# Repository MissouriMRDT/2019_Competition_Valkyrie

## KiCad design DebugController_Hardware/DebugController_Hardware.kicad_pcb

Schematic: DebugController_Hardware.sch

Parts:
C1, C2: 10uf; C_0603_1608Metric_Pad1.05x0.95mm_HandSolder
Conn1: AndersonPP; Anderson_2_Horisontal_Side_by_Side
D1, D2, D3, D4, D5, D6, D7, D8, D9, D10, D11, D12, D13, D14, D15, D16, D17, D18, D19, D20, D21, D22, D23, D24, D25, D26, D27, D28, D30: LED; LED_0603_1608Metric_Pad1.05x0.95mm_HandSolder
R1, R2, R3, R4, R5, R6, R7, R8, R9, R10, R11, R12, R13, R14, R15, R16, R17, R18, R19, R20, R21, R22, R23, R24, R25, R26, R27, R28, R29: 500; R_0603_1608Metric_Pad1.05x0.95mm_HandSolder
RV1: R_POT; Potentiometer_Bourns_PTV09A-1_Single_Vertical
SW1, SW2, SW3, SW4, SW5, SW6, SW7, SW8, SW9, SW10, SW11, SW12, SW13, SW14, SW15, SW16, SW17, SW18, SW19, SW20, SW21, SW22, SW23: SW_Push; SW_SPST_PTS645
U1: TM4C129E_Launchpad; TM4C129E_Launchpad_FULL_Bottom_SMD
U2: OKI; OKI_Horizontal

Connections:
+3V3: C2.1, R5.1, RV1.1, SW1.1, SW2.1, SW3.1, SW4.1, SW5.1, SW6.1, SW7.1, SW8.1, SW9.1, SW10.1, SW11.1, SW12.1, SW13.1, SW14.1, SW15.1, SW16.1, SW17.1, SW18.1, SW19.1, SW20.1, SW21.1, SW22.1, SW23.1, U1.+3V3, U2.3 (Vo)
Arm_1: R12.1, SW7.2, U1.PE0
Arm_2: R13.1, SW8.2, U1.PE1
Arm_3: R14.1, SW9.2, U1.PE2
Arm_4: R15.1, SW10.2, U1.PE3
Arm_5: R17.1, SW11.2, U1.PD7
Arm_6: R18.1, SW12.2, U1.PA6
Arm_7: R19.1, SW13.2, U1.PM4
Arm_8: R20.1, SW14.2, U1.PM5
Arm_Ind: R10.1, U1.PB5
Drive_1: R1.1, SW1.2, U1.PE4
Drive_2: R3.1, SW2.2, U1.PC4
Drive_3: R4.1, SW3.2, U1.PC5
Drive_4: R7.1, SW4.2, U1.PC6
Drive_5: R8.1, SW5.2, U1.PE5
Drive_6: R9.1, SW6.2, U1.PD3
Drive_Ind: R6.1, U1.PB4
unnamed: C1.1, U2.1 (Vi)
unnamed: D1.2 (A), R2.2
unnamed: D2.2 (A), R1.2
unnamed: D3.2 (A), R3.2
unnamed: D4.2 (A), R4.2
unnamed: D5.2 (A), R5.2
unnamed: D6.2 (A), R6.2
unnamed: D7.2 (A), R7.2
unnamed: D8.2 (A), R8.2
unnamed: D9.2 (A), R9.2
unnamed: D10.2 (A), R10.2
unnamed: D11.2 (A), R11.2
unnamed: D12.2 (A), R12.2
unnamed: D13.2 (A), R13.2
unnamed: D14.2 (A), R14.2
unnamed: D15.2 (A), R15.2
unnamed: D16.2 (A), R16.2
unnamed: D17.2 (A), R17.2
unnamed: D18.2 (A), R18.2
unnamed: D19.2 (A), R19.2
unnamed: D20.2 (A), R20.2
unnamed: D21.2 (A), R21.2
unnamed: D22.2 (A), R22.2
unnamed: D23.2 (A), R23.2
unnamed: D24.2 (A), R24.2
unnamed: D25.2 (A), R25.2
unnamed: D26.2 (A), R26.2
unnamed: D27.2 (A), R27.2
unnamed: D28.2 (A), R28.2
unnamed: D30.2 (A), R29.2
Other_1: R25.1, SW19.2, U1.PD1
Other_2: R26.1, SW20.2, U1.PD0
Other_3: R27.1, SW21.2, U1.PN2
Other_4: R28.1, SW22.2, U1.PN3
Other_Ind: R16.1, U1.PK1
Pot_Ind: R2.1, U1.PA5
Pot_Out: RV1.2, U1.PD5
SRA_1: R21.1, SW15.2, U1.PF1
SRA_2: R22.1, SW16.2, U1.PF2
SRA_3: R23.1, SW17.2, U1.PF3
SRA_4: R24.1, SW18.2, U1.PG0
SRA_Ind: R11.1, U1.PK0
Stop: R29.1, SW23.2

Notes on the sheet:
Yellow
Drive System
Arm System
Buttons
SRA System
Other Systems
TIVAs
Stop
Potentiometer
3.3V
Power Conversion
Green
Power
Pot_Ind
LEDs
Blue
Drive
Arm
SRA
Other

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
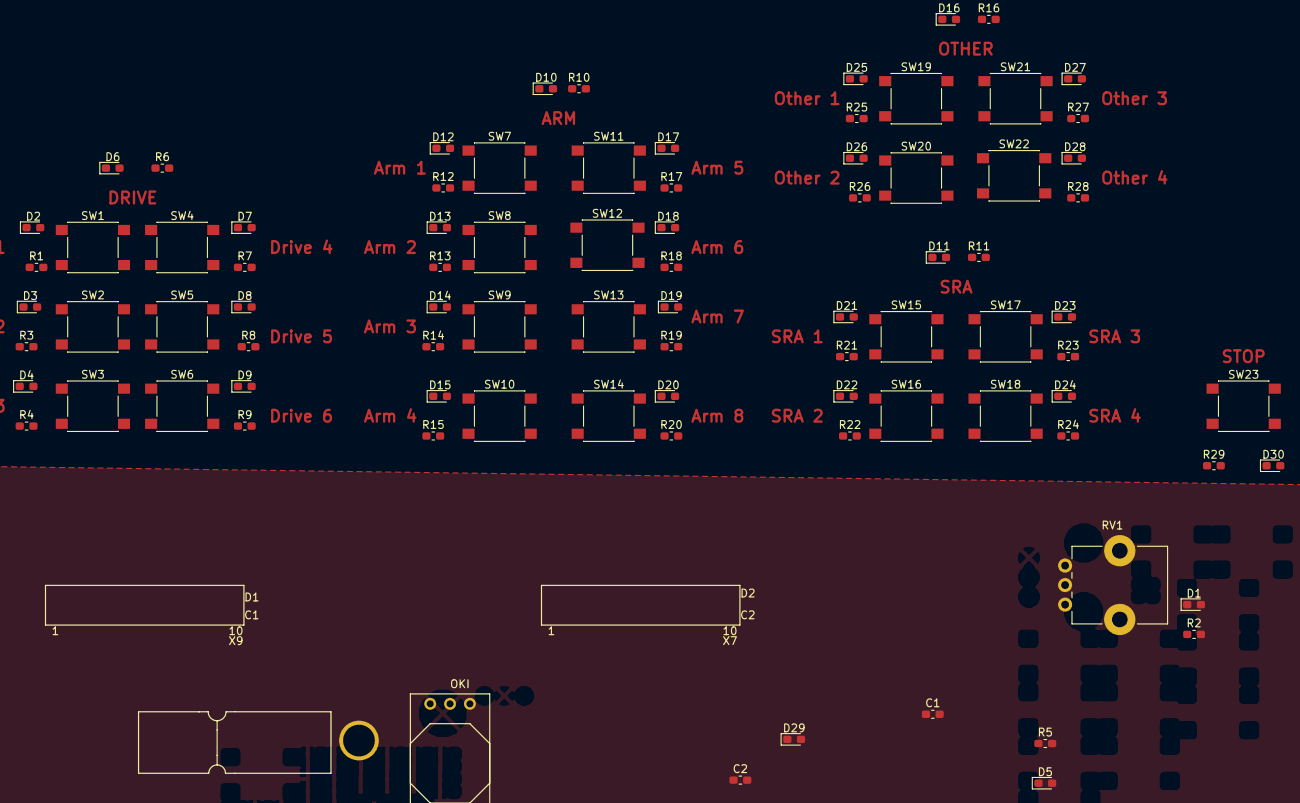
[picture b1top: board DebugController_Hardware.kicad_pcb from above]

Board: 2 copper layers, 88 parts (0 on the bottom side), 61 nets, no tracks yet.

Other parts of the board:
D29: LED; LED_0603_1608Metric_Pad1.05x0.95mm_HandSolder

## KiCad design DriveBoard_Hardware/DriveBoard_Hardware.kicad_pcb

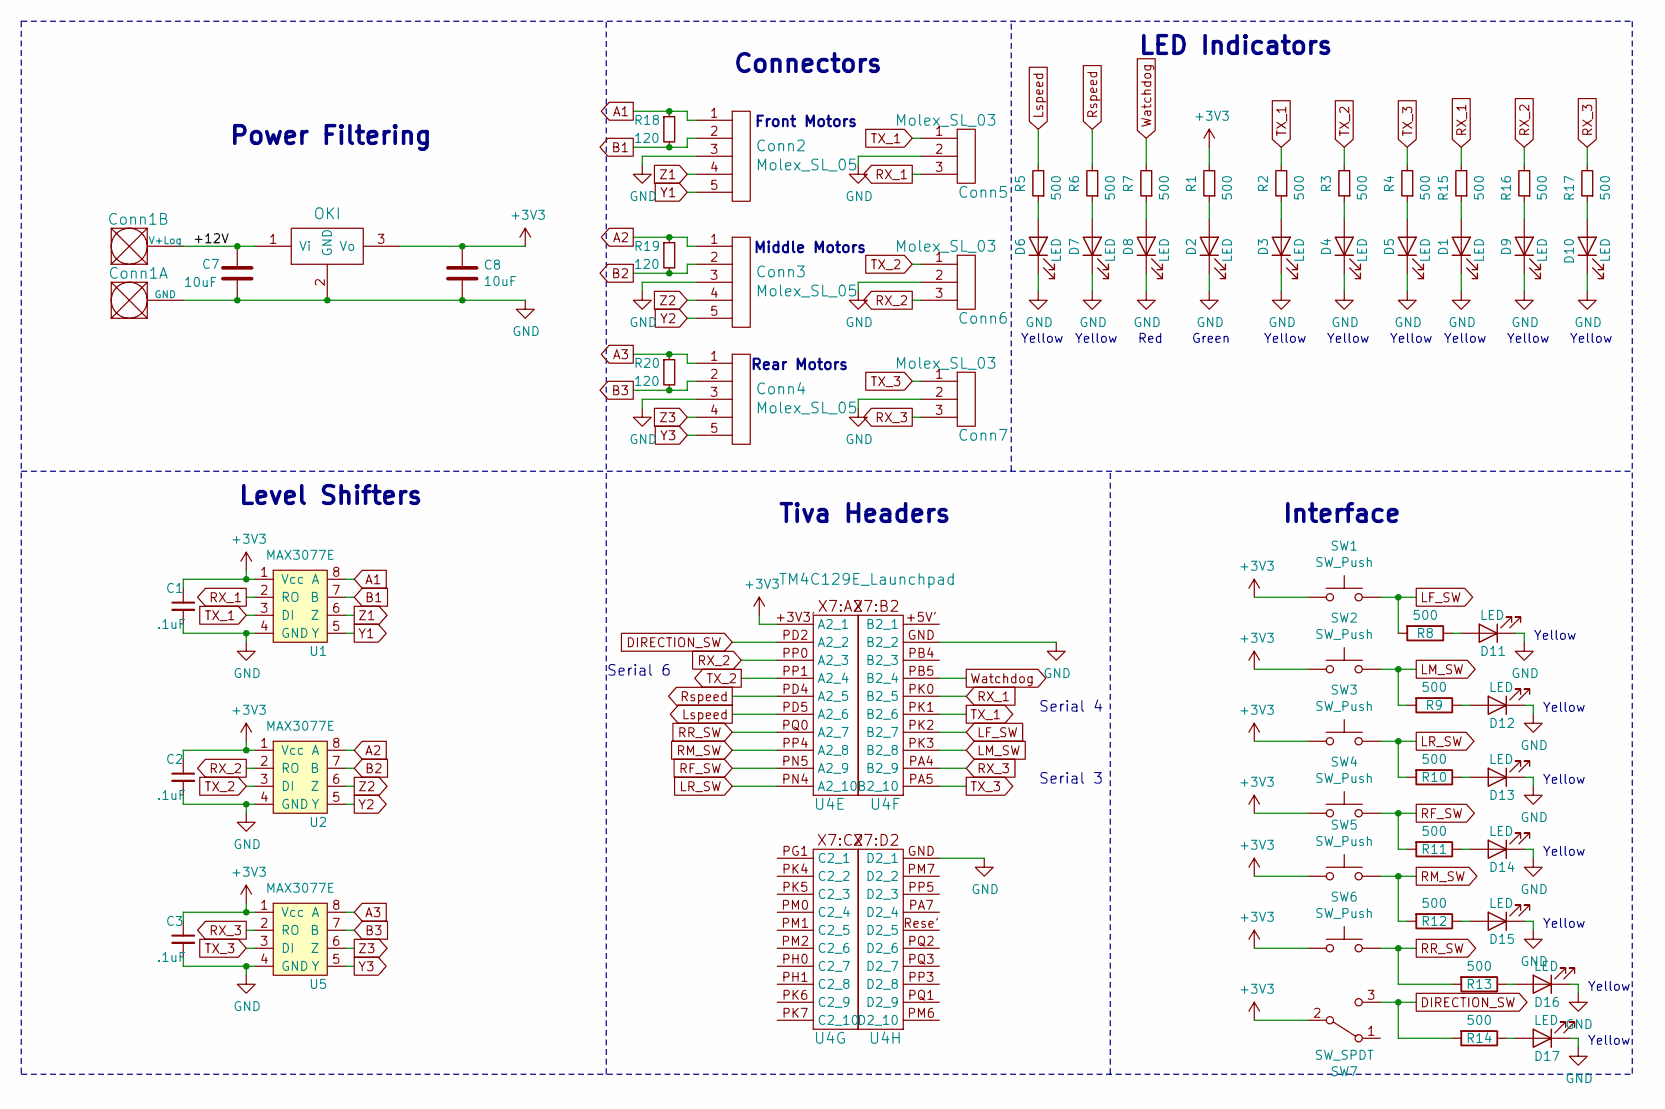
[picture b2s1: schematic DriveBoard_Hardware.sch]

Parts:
C1, C2, C3: .1uF; C_0603_1608Metric_Pad1.05x0.95mm_HandSolder
C7, C8: 10uF; C_0603_1608Metric_Pad1.05x0.95mm_HandSolder
Conn1: AndersonPP; Anderson_2_Horizontal_Side_by_Side
Conn2, Conn3, Conn4: Molex_SL_05; MOLEX_SL_05_Horizontal
Conn5, Conn6, Conn7: Molex_SL_03; MOLEX_SL_03_Horizontal
D1, D2, D3, D4, D5, D6, D7, D8, D9, D10, D11, D12, D13, D14, D15, D16, D17: LED; LED_0603_1608Metric_Pad1.05x0.95mm_HandSolder
R1, R2, R3, R4, R5, R6, R7, R15, R16, R17: 500; LED_0603_1608Metric_Pad1.05x0.95mm_HandSolder
R8, R9, R10, R11, R12, R13, R14: 500; R_0603_1608Metric_Pad1.05x0.95mm_HandSolder
R18, R19, R20: 120; R_0603_1608Metric_Pad1.05x0.95mm_HandSolder
SW1, SW2, SW3, SW4, SW5, SW6: SW_Push; SW_SPST_TL3305A
SW7: SW_SPDT; SW_CuK_OS102011MA1QN1_SPDT_Angled
U1, U2, U5: MAX3077E; SOIC-8_3.9x4.9mm_P1.27mm
U3: OKI; OKI_Horizontal
U4: TM4C129E_Launchpad; TM4C129E_Launchpad_X7_SMD_BOTTOM

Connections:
+3V3: C1.1, C2.1, C3.1, C8.1, R1.2, SW1.1, SW2.1, SW3.1, SW4.1, SW5.1, SW6.1, SW7.2 (B), U1.1 (Vcc), U2.1 (Vcc), U3.3 (Vo), U4.+3V3' (A2_1), U5.1 (Vcc)
/+12V: C7.1, Conn1.2 (V+Log), U3.1 (Vi)
A1: Conn2.1, R18.1, U1.8 (A)
A2: Conn3.1, R19.1, U2.8 (A)
A3: Conn4.1, R20.1, U5.8 (A)
B1: Conn2.2, R18.2, U1.7 (B)
B2: Conn3.2, R19.2, U2.7 (B)
B3: Conn4.2, R20.2, U5.7 (B)
DIRECTION_SW: R14.2, SW7.3 (C), U4.PD2 (A2_2)
GND: C1.2, C2.2, C3.2, C7.2, C8.2, Conn1.1 (GND), Conn2.3, Conn3.3, Conn4.3, Conn5.2, Conn6.2, Conn7.2, D1.1 (K), D2.1 (K), D3.1 (K), D4.1 (K), D5.1 (K), D6.1 (K), D7.1 (K), D8.1 (K), D9.1 (K), D10.1 (K), D11.1 (K), D12.1 (K), D13.1 (K), D14.1 (K), D15.1 (K), D16.1 (K), D17.1 (K), U1.4 (GND), U2.4 (GND), U3.2 (GND), U4.GND (B1_2), U5.4 (GND)
LF_SW: R8.2, SW1.2, U4.PK2 (B2_7)
LM_SW: R9.2, SW2.2, U4.PK3 (B2_8)
LR_SW: R10.2, SW3.2, U4.PN4 (A2_10)
Lspeed: R5.2, U4.PD5 (A2_6)
unnamed: D1.2 (A), R15.1
unnamed: D2.2 (A), R1.1
unnamed: D3.2 (A), R2.1
unnamed: D4.2 (A), R3.1
unnamed: D5.2 (A), R4.1
unnamed: D6.2 (A), R5.1
unnamed: D7.2 (A), R6.1
unnamed: D8.2 (A), R7.1
unnamed: D9.2 (A), R16.1
unnamed: D10.2 (A), R17.1
unnamed: D11.2 (A), R8.1
unnamed: D12.2 (A), R9.1
unnamed: D13.2 (A), R10.1
unnamed: D14.2 (A), R11.1
unnamed: D15.2 (A), R12.1
unnamed: D16.2 (A), R13.1
unnamed: D17.2 (A), R14.1
RF_SW: R11.2, SW4.2, U4.PN5 (A2_9)
RM_SW: R12.2, SW5.2, U4.PP4 (A2_8)
RR_SW: R13.2, SW6.2, U4.PQ0 (A2_7)
RX_1: Conn5.3, R15.2, U1.2 (RO), U4.PK0 (B2_5)
RX_2: Conn6.3, R16.2, U2.2 (RO), U4.PP0 (A2_3)
RX_3: Conn7.3, R17.2, U4.PA4 (B2_9), U5.2 (RO)
Rspeed: R6.2, U4.PD4 (A2_5)
TX_1: Conn5.1, R2.2, U1.3 (DI), U4.PK1 (B2_6)
TX_2: Conn6.1, R3.2, U2.3 (DI), U4.PP1 (A2_4)
TX_3: Conn7.1, R4.2, U4.PA5 (B2_10), U5.3 (DI)
Watchdog: R7.2, U4.PB5 (B2_4)
Y1: Conn2.5, U1.5 (Y)
Y2: Conn3.5, U2.5 (Y)
Y3: Conn4.5, U5.5 (Y)
Z1: Conn2.4, U1.6 (Z)
Z2: Conn3.4, U2.6 (Z)
Z3: Conn4.4, U5.6 (Z)

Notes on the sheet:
Connectors
Tiva Headers
Power Filtering
Level Shifters
Front Motors
Middle Motors
Rear Motors
Serial 4
Serial 3
Serial 6
LED Indicators
Interface
Yellow
Green
Red

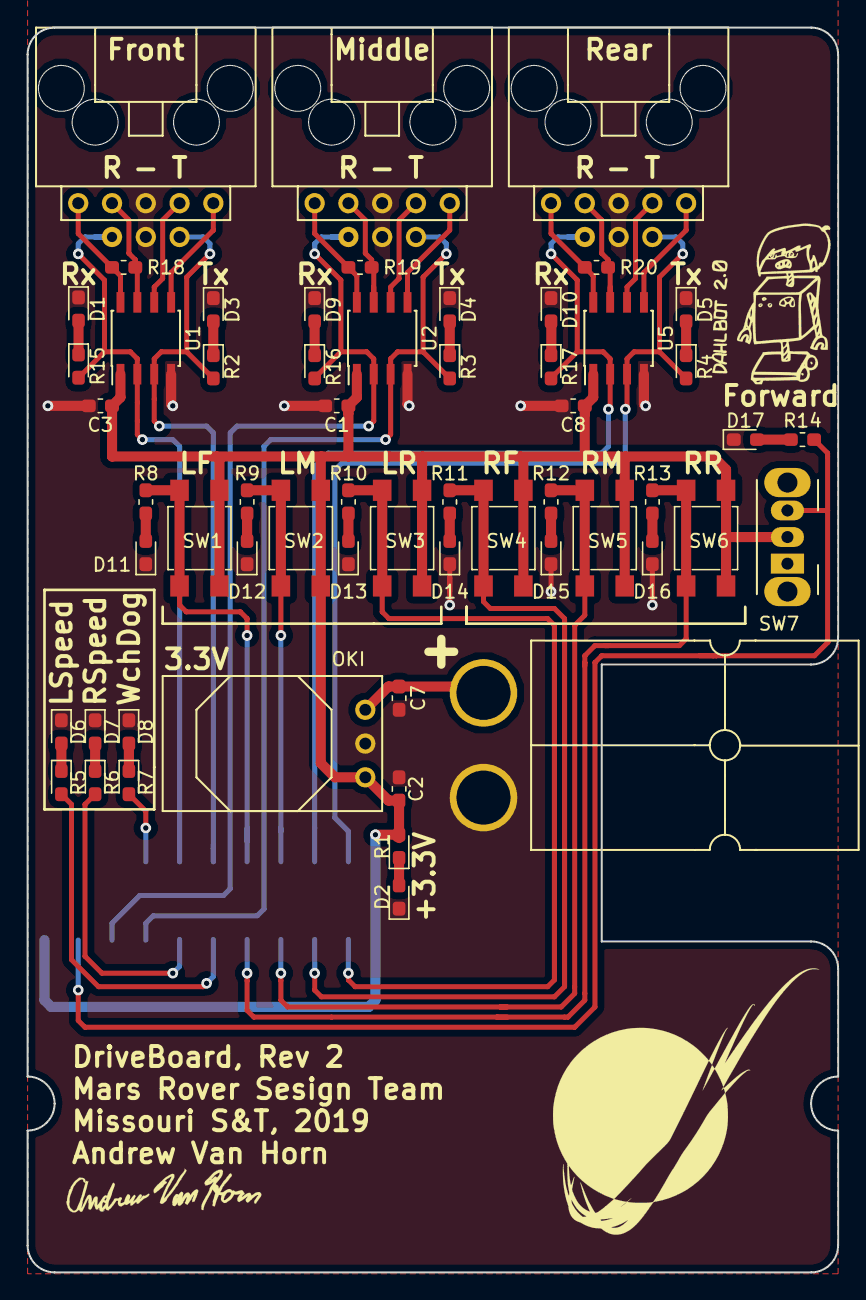
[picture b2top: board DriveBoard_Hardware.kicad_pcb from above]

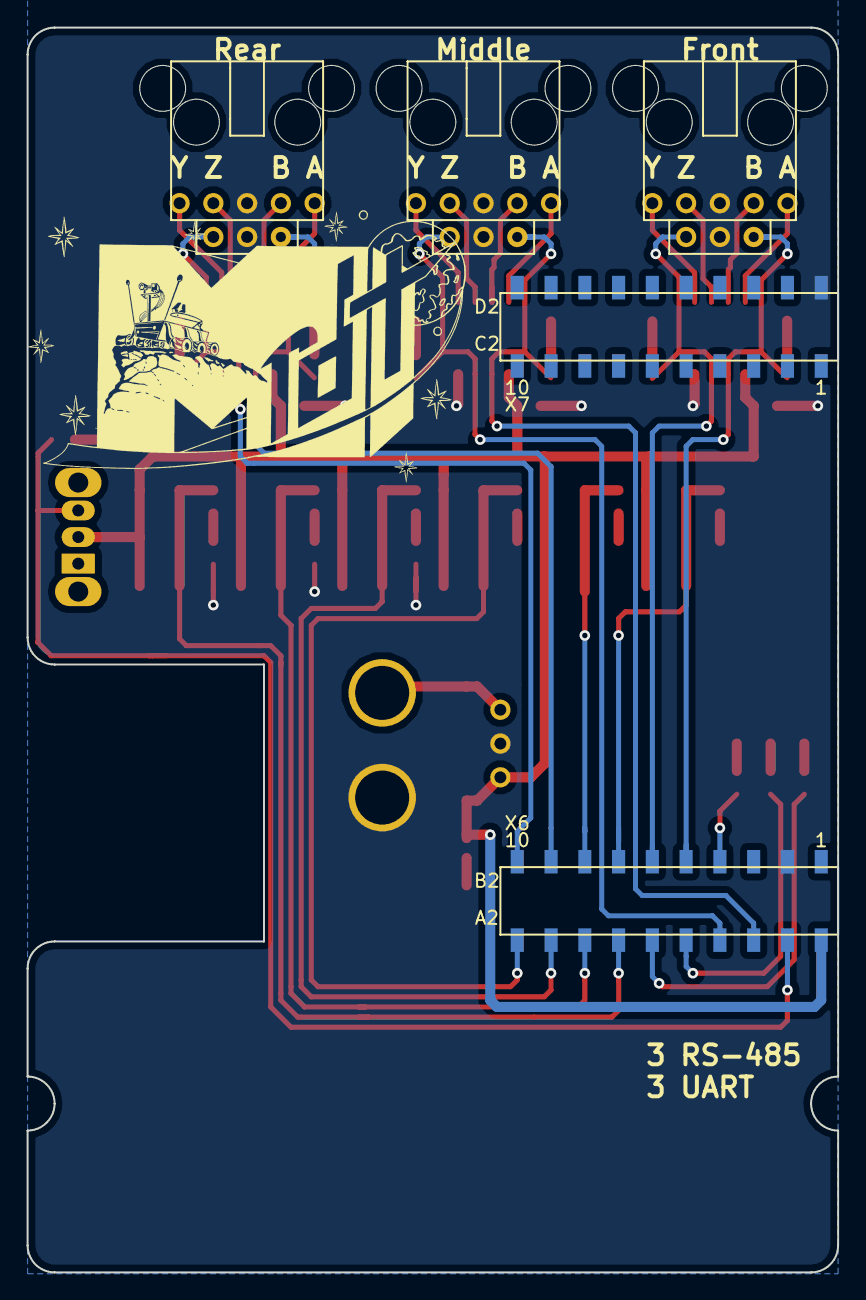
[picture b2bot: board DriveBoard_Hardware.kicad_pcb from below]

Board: 2 copper layers, 61.0 x 93.6 mm, 61 parts (3 on the bottom side), 48 nets.

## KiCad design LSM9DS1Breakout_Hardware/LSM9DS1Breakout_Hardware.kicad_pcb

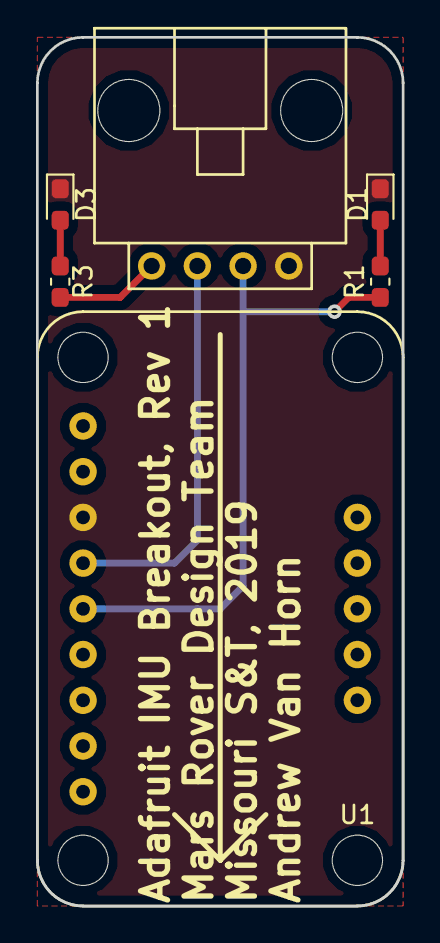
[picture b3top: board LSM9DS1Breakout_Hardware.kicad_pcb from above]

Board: 2 copper layers, 20.3 x 48.3 mm, 6 parts (0 on the bottom side), 6 nets.

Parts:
Conn1: Molex_SL_04; MOLEX_SL_04_Horizontal
D1, D3: LED; LED_0603_1608Metric_Pad1.05x0.95mm_HandSolder
R1, R3: 500; R_0603_1608Metric_Pad1.05x0.95mm_HandSolder
U1: Adafruit_LSM9DS1

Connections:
+5V: Conn1.1, R3.1, U1.1
GND: Conn1.4, D1.1, D3.1, U1.3
unnamed: D1.2, R1.2
unnamed: D3.2, R3.2
SCL: Conn1.2, U1.4
SDA: Conn1.3, R1.1, U1.5

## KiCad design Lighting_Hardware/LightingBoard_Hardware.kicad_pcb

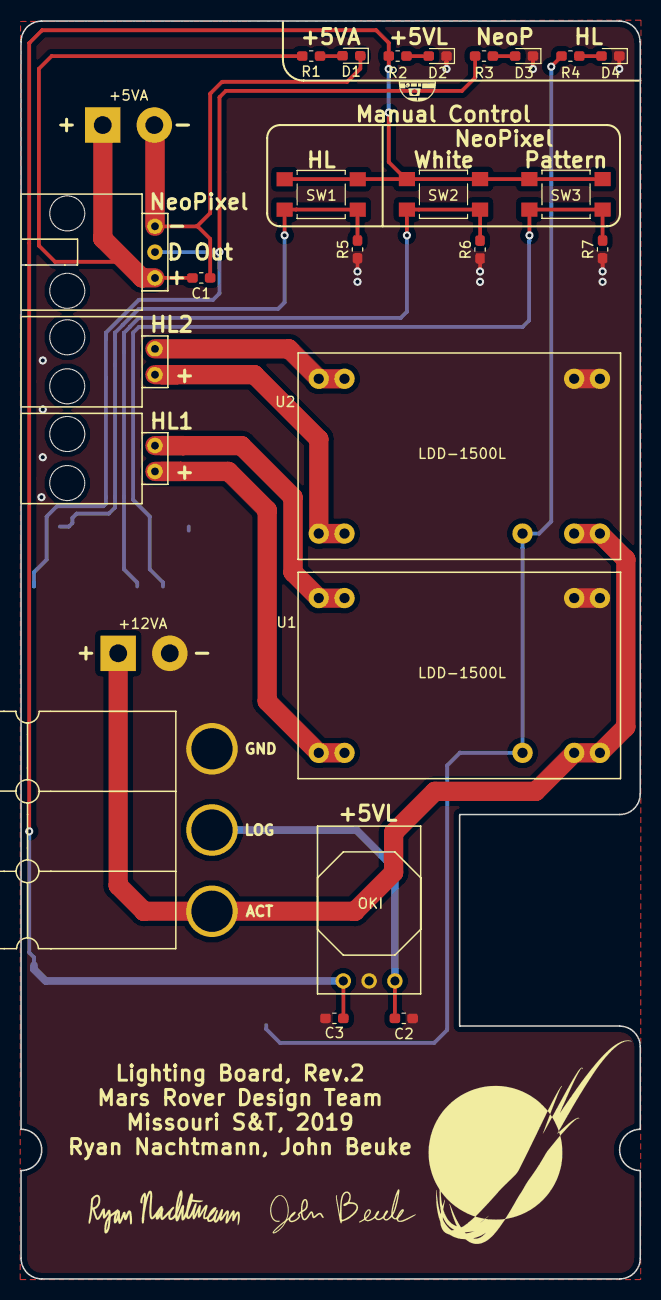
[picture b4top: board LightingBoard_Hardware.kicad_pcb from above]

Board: 2 copper layers, 61.0 x 123.8 mm, 27 parts (0 on the bottom side), 19 nets.

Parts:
+5VA, +12VA: SolderWirePad_1x02_P5.08mm_Drill1.5mm
C1, C2, C3: 10uF; C_0603_1608Metric_Pad1.05x0.95mm_HandSolder
Conn1: AndersonPP; Anderson_3_Horisontal_Side_by_Side
Conn2, Conn3: Molex_SL_02; MOLEX_SL_02_Horizontal
Conn4: Molex_SL_03; MOLEX_SL_03_Horizontal
D1, D2: G_LED; LED_0603_1608Metric_Pad1.05x0.95mm_HandSolder
D3, D4: Org_LED; LED_0603_1608Metric_Pad1.05x0.95mm_HandSolder
R1, R2, R3, R4: 500; R_0603_1608Metric_Pad1.05x0.95mm_HandSolder
R5, R6, R7: 10K; R_0603_1608Metric_Pad1.05x0.95mm_HandSolder
SW1, SW2, SW3: SW_Push; SW_SPST_TL3305A
U1, U2: LDD-1500L; LDD-1500L_LED_DRIVER
U3: TM4C129E_Launchpad; TM4C129E_Launchpad_X9_SMD_BOTTOM
U4: OKI; OKI_Horizontal

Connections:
+5VA: +5VA.1, C1.1, Conn4.1, R1.1
+5VL: C3.1, R2.1, SW1.1, SW2.1, SW3.1, U3.+5V, U4.3
+12VA: +12VA.1, Conn1.3, U1.23, U1.24, U2.23, U2.24
/Headlight_V1+: Conn2.1, U1.13, U1.14
/Headlight_V1-: Conn2.2, U1.11, U1.12
/Headlight_V2+: Conn3.1, U2.13, U2.14
/Headlight_V2-: Conn3.2, U2.11, U2.12
Dout_NeoPixel: Conn4.2, R3.1, U3.PF1
GND: +12VA.2, C2.2, C3.2, Conn1.1, D2.1, D3.1, D4.1, R5.1, R6.1, R7.1, U1.1, U1.2, U2.1, U2.2, U3.GND, U4.2
GNDA: +5VA.2, C1.2, Conn4.3, D1.1
Headlight_OnOff_PWM: R4.1, U1.21, U2.21, U3.PB3
Headlight_Power: R5.2, SW1.2, U3.PM3
NeoPixel_Pattern: R7.2, SW3.2, U3.PL5
NeoPixel_White: R6.2, SW2.2, U3.PL4
unnamed: C2.1, Conn1.2, U4.1
unnamed: D1.2, R1.2
unnamed: D2.2, R2.2
unnamed: D3.2, R3.2
unnamed: D4.2, R4.2

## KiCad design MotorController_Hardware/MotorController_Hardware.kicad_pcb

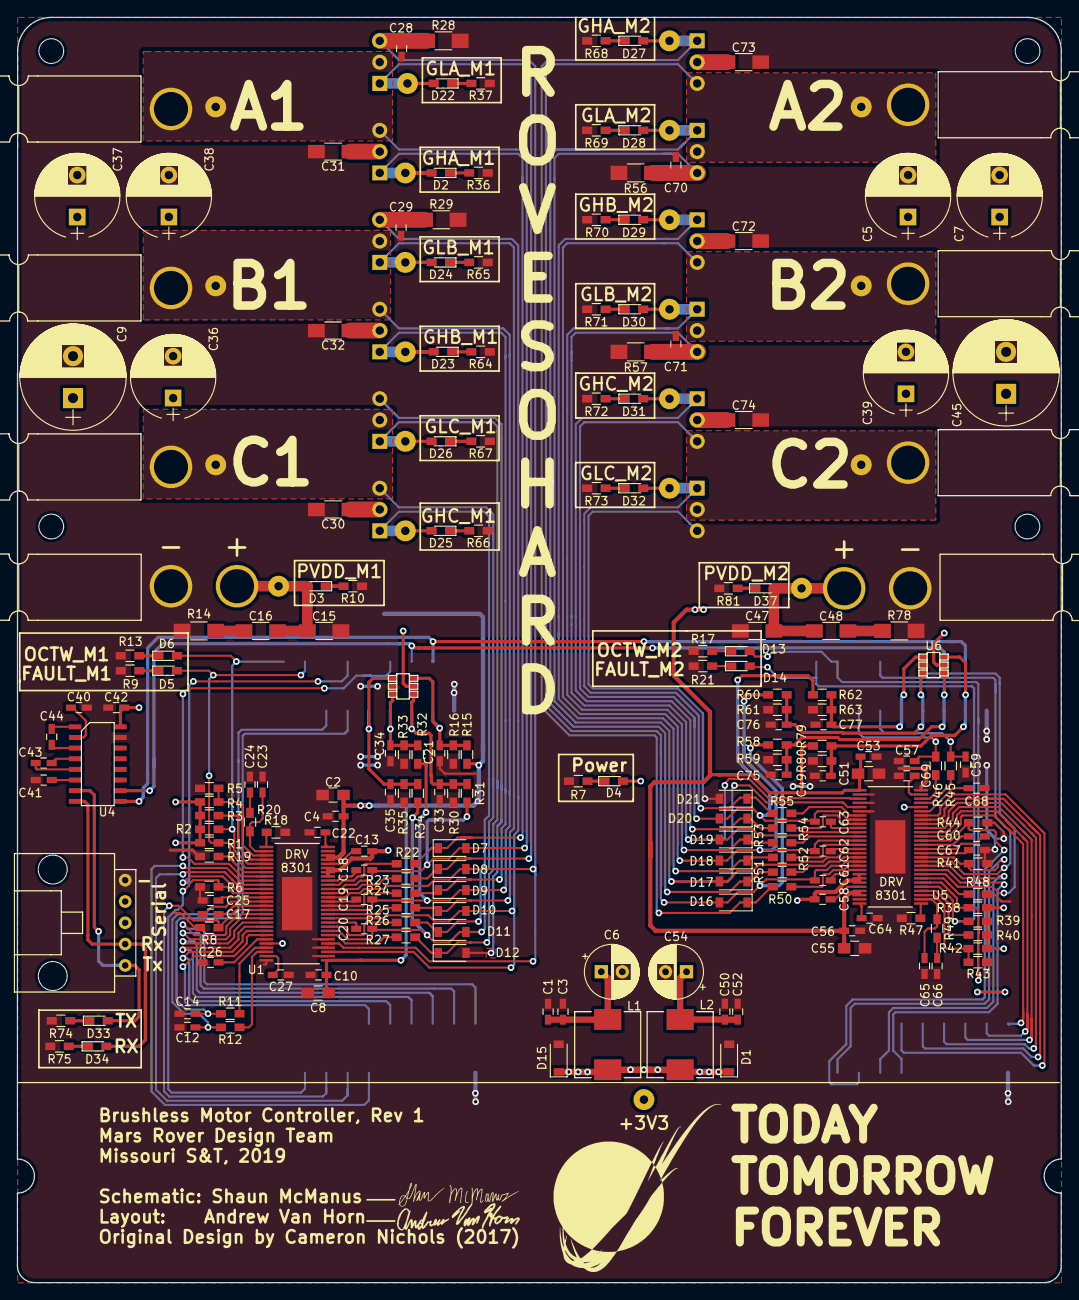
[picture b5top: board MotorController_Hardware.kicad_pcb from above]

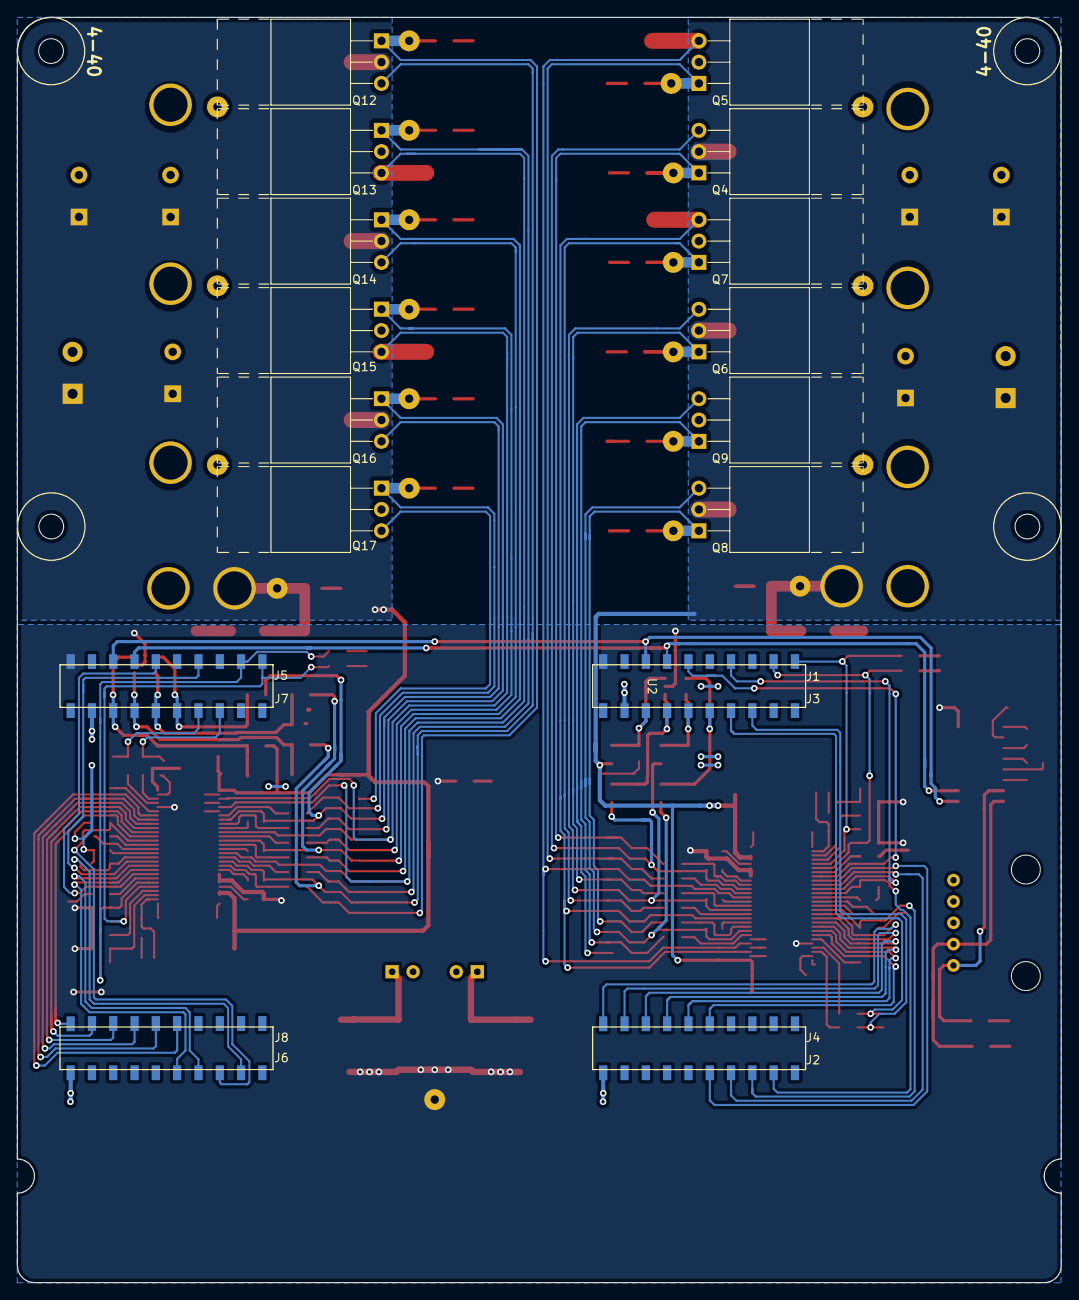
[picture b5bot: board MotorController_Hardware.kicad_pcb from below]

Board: 2 copper layers, 124.5 x 150.9 mm, 239 parts (12 on the bottom side), 149 nets.

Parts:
+3V3: TEST; SolderWirePad_single_1mmDrill
C1, C4, C10, C13, C18, C19, C20, C21, C33, C34, C35, C40, C41, C42, C43, C44, C49, C50, C53, C56, C58, C61, C62, C63, C75, C76, C77: 0.1u; C_0603_HandSoldering
C2, C8, C51, C55: 4.7u; C_0805_HandSoldering
C3, C26, C27, C52, C68, C69: 1u; C_0603_HandSoldering
C5, C7, C36, C37, C38, C39: 220u; CP_Radial_D10.0mm_P5.00mm
C6, C54: 47u; CP_Radial_D6.3mm_P2.50mm
C9, C45: 470u; CP_Radial_D12.5mm_P5.00mm
C12, C14, C57, C59: 2200p; C_0603_HandSoldering
C15, C47: 0.1u; C_1206_HandSoldering
C16, C48: 0.01u; C_1206_HandSoldering
C17, C60: .022u; C_0603_HandSoldering
C22, C64: 0.015u; C_0603_HandSoldering
C23, C65: 120p; C_0603_HandSoldering
C24, C66: 6800p; C_0603_HandSoldering
C25, C67: 2.2u; C_0603_HandSoldering
C28, C29, C70, C71: 1000p; C_0603_HandSoldering
C30, C31, C32, C72, C73, C74: 2.2u; C_1206_HandSoldering
Conn1: Molex_SL_05; MOLEX_SL_05_Horizontal
Conn3, Conn8: AndersonPP; Anderson_2_Horizontal_Stacked
Conn4: SH_A_M1_PP; Anderson_1_Horizontal
Conn5: SH_B_M1_PP; Anderson_1_Horizontal
Conn6: SH_C_M1_PP; Anderson_1_Horizontal
Conn9: SH_A_M2_PP; Anderson_1_Horizontal
Conn10: SH_B_M2_PP; Anderson_1_Horizontal
Conn11: SH_C_M2_PP; Anderson_1_Horizontal
D1: D_Shottky; D_SOD-123
D2, D3, D4, D5, D6, D13, D14, D22, D23, D24, D25, D26, D27, D28, D29, D30, D31, D32, D33, D34, D37: LED; LED_0603_HandSoldering
D7, D8, D9, D10, D11, D12, D16, D17, D18, D19, D20, D21: 3.3V; D_SOD-123
D15: D_Schottky; D_SOD-123
GHA_M1: tp; SolderWirePad_single_1mmDrill
GHA_M2: TEST; SolderWirePad_single_1mmDrill
GHB_M1, GHB_M2: TEST; SolderWirePad_single_1mmDrill
GHC_M1, GHC_M2: TEST; SolderWirePad_single_1mmDrill
GLA_M1, GLA_M2: TEST; SolderWirePad_single_1mmDrill
GLB_M1, GLB_M2: TEST; SolderWirePad_single_1mmDrill
GLC_M1, GLC_M2: TEST; SolderWirePad_single_1mmDrill
L1, L2: 33u; DR74_330_R
PVDD_M1, PVDD_M2: TEST; SolderWirePad_single_1mmDrill
Q4, Q5, Q6, Q7, Q8, Q9, Q12, Q13, Q14, Q15, Q16, Q17: FQP30N06L; TO-220-3_Horizontal_Reversed_NoHole
R1, R2, R3, R5, R38, R39, R40, R43: 10k; R_0603_HandSoldering
R4, R42: 31.6k; R_0603_HandSoldering
R6, R8, R41, R44: 1k; R_0603_HandSoldering
R7, R9, R13, R17, R21, R36, R37, R64, R65, R66, R67, R68, R69, R70, R71, R72, R73, R74, R75: 500; R_0603_HandSoldering
R10, R81: 1.5K; R_0603_HandSoldering
R11, R12, R45, R46: 56; R_0603_HandSoldering
R14, R78: 3.3; R_1206_HandSoldering
R15, R30, R32, R34, R58, R60, R62, R79: 46.4k; R_0603_HandSoldering
R16, R31, R33, R35, R59, R61, R63, R80: 4.99k; R_0603_HandSoldering
R18, R47: 205k; R_0603_HandSoldering
R19, R48: 150k; R_0603_HandSoldering
R20, R49: 16.2k; R_0603_HandSoldering
R22, R23, R24, R25, R26, R27, R50, R51, R52, R53, R54, R55: 10; R_0603_HandSoldering
R28, R29, R56, R57: .001; R_1206_HandSoldering
SHA_M1, SHA_M2: TEST; SolderWirePad_single_1mmDrill
SHB_M1, SHB_M2: TEST; SolderWirePad_single_1mmDrill
SHC_M1, SHC_M2: TEST; SolderWirePad_single_1mmDrill
U1, U5: DRV8301
U2, U6: NUP4201MR6
U3: LAUNCHXL_F28069M_Launchpad; LAUNCHXL_F28069M_FULL_SMD_BOTTOM
U4: MAX_3232; SOIC_16_3.9x9.9mm_Pitch1.27mm

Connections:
+3V3: +3V3.1, C13.1, C42.2, C58.1, D1.1, D4.2, D15.1, L1.2, L2.2, R1.1, R2.1, R3.1, R4.1, R38.1, R39.1, R40.1, R42.1, U1.24, U1.49, U1.50, U1.51, U2.2, U3.+3V3, U3.+3V3`, U4.16, U5.24, U5.49, U5.50, U5.51, U6.2
ASENSE_M1: C33.1, R30.2, R31.1, U2.1, U3.A_B1
ASENSE_M2: C75.1, R58.2, R59.1, U3.A_B4, U6.1
BSENSE_M1: C34.1, R32.2, R33.1, U2.6, U3.A_A2
BSENSE_M2: C76.1, R60.2, R61.1, U3.A_A5, U6.6
CSENSE_M1: C35.1, R34.2, R35.1, U2.4, U3.A_B2
CSENSE_M2: C77.1, R62.2, R63.1, U3.A_B5, U6.4
DC_CAL_M1: R6.1, U1.12, U3.P_51
DC_CAL_M2: R41.1, U3.P_53, U5.12
EN_GATE_M1: R8.1, U1.16, U3.P_50
EN_GATE_M2: R44.1, U3.P_52, U5.16
GH_A_M1: R22.2, U1.47
GH_A_M2: R50.2, U5.47
GH_B_M1: R24.2, U1.42
GH_B_M2: R52.2, U5.42
GH_C_M1: R26.2, U1.37
GH_C_M2: R54.2, U5.37
GL_A_M1: R23.2, U1.45
GL_A_M2: R51.2, U5.45
GL_B_M1: R25.2, U1.40
GL_B_M2: R53.2, U5.40
GL_C_M1: R27.2, U1.35
GL_C_M2: R55.2, U5.35
GND: C1.2, C2.2, C3.2, C4.2, C5.2, C6.2, C7.2, C8.2, C9.2, C10.2, C12.2, C14.2, C15.2, C21.2, C22.1, C23.1, C24.1, C25.1, C26.1, C27.1, C28.2, C29.2, C30.2, C31.2, C32.2, C33.2, C34.2, C35.2, C36.2, C37.2, C38.2, C39.2, C40.1, C41.2, C42.1, C45.2, C47.2, C49.2, C50.2, C51.2, C52.2, C53.2, C54.2, C55.2, C56.2, C57.2, C59.2, C64.1, C65.2, C66.2, C67.1, C68.1, C69.1, C70.2, C71.2, C72.2, C73.2, C74.2, C75.2, C76.2, C77.2, Conn1.5, Conn3.1, Conn8.1, D1.2, D12.2, D15.2, D21.2, Q9.3, Q17.3, R5.2, R6.2, R7.1, R8.2, R9.1, R10.1, R13.1, R14.2, R16.2, R17.1, R18.2, R19.2, R21.1, R28.2, R29.2, R31.2, R33.2, R35.2, R36.1, R37.1, R41.2, R43.2, R44.2, R47.2, R48.2, R56.2, R57.2, R59.2, R61.2, R63.2, R64.1, R65.1, R66.1, R67.1, R68.1, R69.1, R70.1, R71.1, R72.1, R73.1, R74.1, R75.1, R78.2, R80.2, R81.1, U1.28, U1.30, U1.32, U1.34, U1.57, U2.5, U3.GND, U4.15, U5.28, U5.30, U5.32, U5.34, U5.57, U6.5
INH_A_M1: U1.17, U3.P_0
INH_A_M2: U3.P_6, U5.17
INH_B_M1: U1.19, U3.P_2
INH_B_M2: U3.P_8, U5.19
INH_C_M1: U1.21, U3.P_4
INH_C_M2: U3.P_10, U5.21
INL_A_M1: U1.18, U3.P_1
INL_A_M2: U3.P_7, U5.18
INL_B_M1: U1.20, U3.P_3
INL_B_M2: U3.P_9, U5.20
INL_C_M1: U1.22, U3.P_5
INL_C_M2: U3.P_11, U5.22
MGH_A_M1: D2.2, D7.1, GHA_M1.1, Q4.1, R22.1
MGH_A_M2: D16.1, D27.2, GHA_M2.1, Q12.1, R50.1
MGH_B_M1: D9.1, D23.2, GHB_M1.1, Q6.1, R24.1
MGH_B_M2: D18.1, D29.2, GHB_M2.1, Q14.1, R52.1
MGH_C_M1: D11.1, D25.2, GHC_M1.1, Q8.1, R26.1
MGH_C_M2: D20.1, D31.2, GHC_M2.1, Q16.1, R54.1
MGL_A_M1: D8.1, D22.2, GLA_M1.1, Q5.1, R23.1
MGL_A_M2: D17.1, D28.2, GLA_M2.1, Q13.1, R51.1
MGL_B_M1: D10.1, D24.2, GLB_M1.1, Q7.1, R25.1
MGL_B_M2: D19.1, D30.2, GLB_M2.1, Q15.1, R53.1
MGL_C_M1: D12.1, D26.2, GLC_M1.1, Q9.1, R27.1
MGL_C_M2: D21.1, D32.2, GLC_M2.1, Q17.1, R55.1
NFAULT_M1: D5.2, R1.2, U1.6, U3.P_33
NFAULT_M2: D13.2, R38.2, U3.P_23, U5.6
NOCTW_M1: D6.2, R2.2, U1.5, U3.P_32
NOCTW_M2: D14.2, R39.2, U3.P_54, U5.5
NSCS_M1: U1.8, U3.P_12
NSCS_M2: U3.P_20, U5.8
unnamed: C1.1, C3.1, C6.1, L1.1
unnamed: C13.2, U1.52
unnamed: C16.2, R14.1
unnamed: C17.1, U1.15
unnamed: C17.2, U1.14
unnamed: C18.1, U1.48
unnamed: C19.1, U1.43
unnamed: C20.1, U1.38
unnamed: C22.2, U1.56
unnamed: C23.2, R20.2, U1.2
unnamed: C24.2, R20.1
unnamed: C25.2, U1.13
unnamed: C26.2, U1.23
unnamed: C27.2, U1.27
unnamed: C40.2, U4.2
unnamed: C41.1, U4.6
unnamed: C43.1, U4.4
unnamed: C43.2, U4.5
unnamed: C44.1, U4.1
unnamed: C44.2, U4.3
unnamed: C48.2, R78.1
unnamed: C50.1, C52.1, C54.1, L2.1
unnamed: C58.2, U5.52
unnamed: C60.1, U5.15
unnamed: C60.2, U5.14
unnamed: C61.1, U5.48
unnamed: C62.1, U5.43
unnamed: C63.1, U5.38
unnamed: C64.2, U5.56
unnamed: C65.1, R49.1, U5.2
unnamed: C66.1, R49.2
unnamed: C67.2, U5.13
unnamed: C68.2, U5.23
unnamed: C69.2, U5.27
unnamed: D2.1, R36.2
unnamed: D3.1, R10.2
unnamed: D4.1, R7.2
unnamed: D5.1, R9.2
unnamed: D6.1, R13.2
unnamed: D13.1, R17.2
unnamed: D14.1, R21.2
unnamed: D22.1, R37.2
unnamed: D23.1, R64.2
unnamed: D24.1, R65.2
unnamed: D25.1, R66.2
unnamed: D26.1, R67.2
unnamed: D27.1, R68.2
unnamed: D28.1, R69.2
unnamed: D29.1, R70.2
unnamed: D30.1, R71.2
unnamed: D31.1, R72.2
unnamed: D32.1, R73.2
unnamed: D33.1, R74.2
unnamed: D34.1, R75.2
unnamed: D37.1, R81.2
unnamed: R4.2, R5.1, U1.3
unnamed: R11.2, U1.25
unnamed: R12.1, U1.26
unnamed: R18.1, U1.1
unnamed: R19.1, U1.7
unnamed: R42.2, R43.1, U5.3
unnamed: R45.2, U5.25
unnamed: R46.1, U5.26
unnamed: R47.1, U5.1
unnamed: R48.1, U5.7
PVDDSENSE_M1: C21.1, R15.2, R16.1, U2.3, U3.A_A7
PVDDSENSE_M2: C49.1, R79.2, R80.1, U3.A_B7, U6.3
PVDD_M1: C2.1, C4.1, C8.1, C9.1, C10.1, C15.1, C16.1, C30.1, C31.1, C32.1, C36.1, C37.1, C38.1, Conn3.4, D3.2, PVDD_M1.1, Q4.2, Q6.2, Q8.2, R15.1, U1.29, U1.53, U1.54
PVDD_M2: C5.1, C7.1, C39.1, C45.1, C47.1, C48.1, C51.1, C53.1, C55.1, C56.1, C72.1, C73.1, C74.1, Conn8.4, D37.2, PVDD_M2.1, Q12.2, Q14.2, Q16.2, R79.1, U5.29, U5.53, U5.54
PWRGD_M1: R3.2, U1.4
PWRGD_M2: R40.2, U5.4
SCLK_M1: U1.11, U3.P_18
SCLK_M2: U3.P_14, U5.11
SDI_M1: U1.9, U3.P_16
SDI_M2: U3.P_24, U5.9
SDO_M1: U1.10, U3.P_17
SDO_M2: U3.P_25, U5.10
SH_A_M1: C18.2, Conn4.1, D7.2, Q4.3, Q5.2, R30.1, SHA_M1.1, U1.46
SH_A_M2: C61.2, Conn9.1, D16.2, Q12.3, Q13.2, R58.1, SHA_M2.1, U5.46
SH_B_M1: C19.2, Conn5.1, D9.2, Q6.3, Q7.2, R32.1, SHB_M1.1, U1.41
SH_B_M2: C62.2, Conn10.1, D18.2, Q14.3, Q15.2, R60.1, SHB_M2.1, U5.41
SH_C_M1: C20.2, Conn6.1, D11.2, Q8.3, Q9.2, R34.1, SHC_M1.1, U1.36
SH_C_M2: C63.2, Conn11.1, D20.2, Q16.3, Q17.2, R62.1, SHC_M2.1, U5.36
SL_A_M1: C28.1, D8.2, Q5.3, R28.1, U1.33, U1.44
SL_A_M2: C70.1, D17.2, Q13.3, R56.1, U5.33, U5.44
SL_B_M1: C29.1, D10.2, Q7.3, R29.1, U1.31, U1.39
SL_B_M2: C71.1, D19.2, Q15.3, R57.1, U5.31, U5.39
SL_RX: Conn1.2, D34.2, U4.8
SL_TX: Conn1.1, D33.2, U4.7
SO1_M1: C14.1, R11.1, U3.A_A0
SO1_M2: C59.1, R45.1, U3.A_A3
SO2_M1: C12.1, R12.2, U3.A_B0
SO2_M2: C57.1, R46.2, U3.A_B3
UART_RX: U3.P_15, U3.P_28, U4.9
UART_TX: U3.P_29, U3.P_58, U4.10

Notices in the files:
parts and their libraries:
Copyright 2016 Accelerated Designs. All rights reserved.
